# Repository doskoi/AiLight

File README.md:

# AiLight
Low power Light on Arduino, Hardware and Software (Minimal requirement: LED Stripe with PIR Sensor on ATTiny13)

#### PCB

#### Demo

#### BOM

[CSV](KiCad%20Files/AILight.csv)

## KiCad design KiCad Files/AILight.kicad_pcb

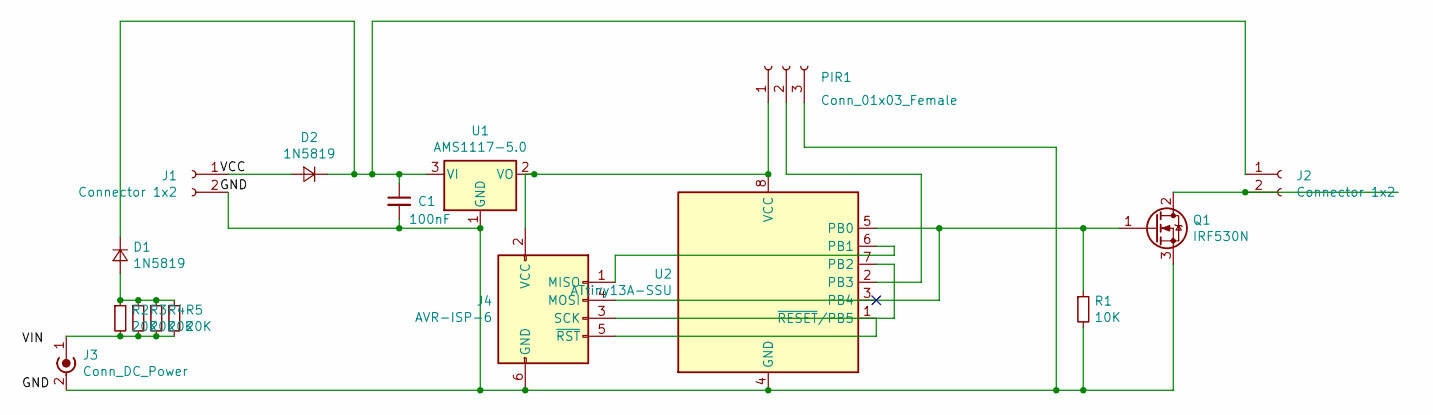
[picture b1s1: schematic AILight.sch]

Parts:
C1: 100nF; C_0805_2012Metric_Pad1.15x1.40mm_HandSolder
D1, D2: 1N5819; D_DO-41_SOD81_P7.62mm_Horizontal
J1, J2: Connector 1x2; PinSocket_1x02_P2.54mm_Vertical
J3: Conn_DC_Power; BarrelJack_CUI_PJ-063AH_Horizontal
J4: AVR-ISP-6; IDC-Header_2x03_P2.54mm_Vertical
PIR1: Conn_01x03_Female; PinSocket_1x03_P2.54mm_Vertical
Q1: IRF530N; TO-220-3_Vertical
R1: 10K; R_0805_2012Metric_Pad1.15x1.40mm_HandSolder
R2, R3, R4, R5: 20K; R_0805_2012Metric_Pad1.15x1.40mm_HandSolder
U1: AMS1117-5.0; SOT-223-3_TabPin2
U2: ATtiny13A-SSU; SOIC-8_3.9x4.9mm_P1.27mm

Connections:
unnamed: C1.1, D1.1 (K), D2.1 (K), J2.1, U1.3 (VI)
unnamed: C1.2, J1.2, J3.2 (Ext), J4.6 (GND), PIR1.3, Q1.3 (S), R1.2, U1.1 (GND), U2.4 (GND)
unnamed: D1.2 (A), R2.1, R3.1, R4.1, R5.1
unnamed: D2.2 (A), J1.1
unnamed: J2.2, Q1.2 (D)
unnamed: J3.1 (In), R2.2, R3.2, R4.2, R5.2
unnamed: J4.1 (MISO), U2.6 (PB1)
unnamed: J4.2 (VCC), PIR1.1, U1.2 (VO), U2.8 (VCC)
unnamed: J4.3 (SCK), U2.7 (PB2)
unnamed: J4.4 (MOSI), Q1.1 (G), R1.1, U2.5 (PB0)
unnamed: J4.5 (~RST), U2.1 (~RESET~/PB5)
unnamed: PIR1.2, U2.2 (PB3)

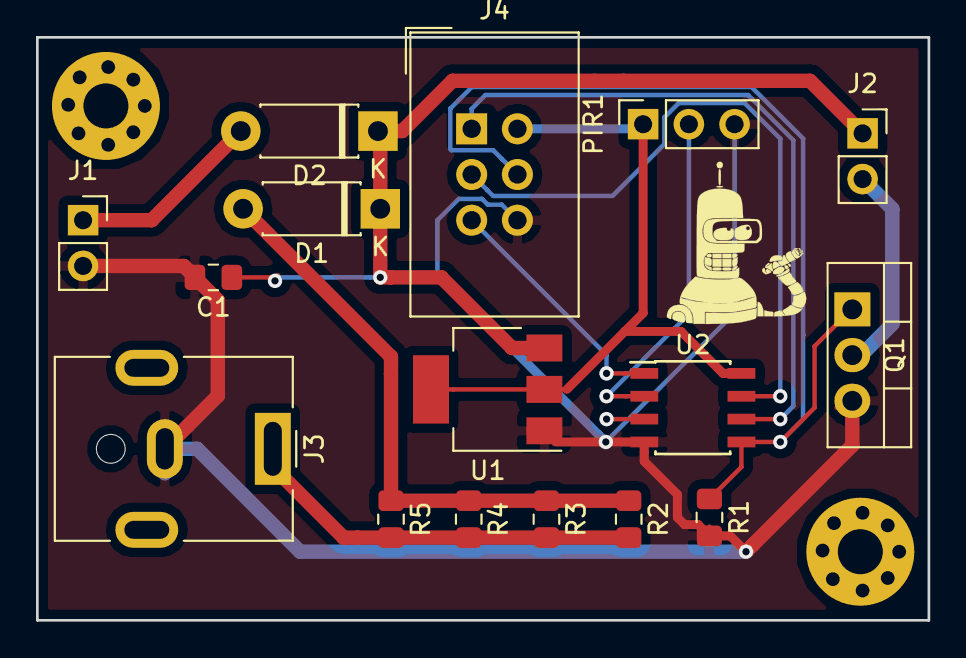
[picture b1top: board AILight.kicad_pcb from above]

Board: 2 copper layers, 49.5 x 32.4 mm, 16 parts (0 on the bottom side), 12 nets.

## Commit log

2018-12-02 Low power (Disable mills to reduce space)
2018-12-02 Initial
2018-12-02 Add PCB files
